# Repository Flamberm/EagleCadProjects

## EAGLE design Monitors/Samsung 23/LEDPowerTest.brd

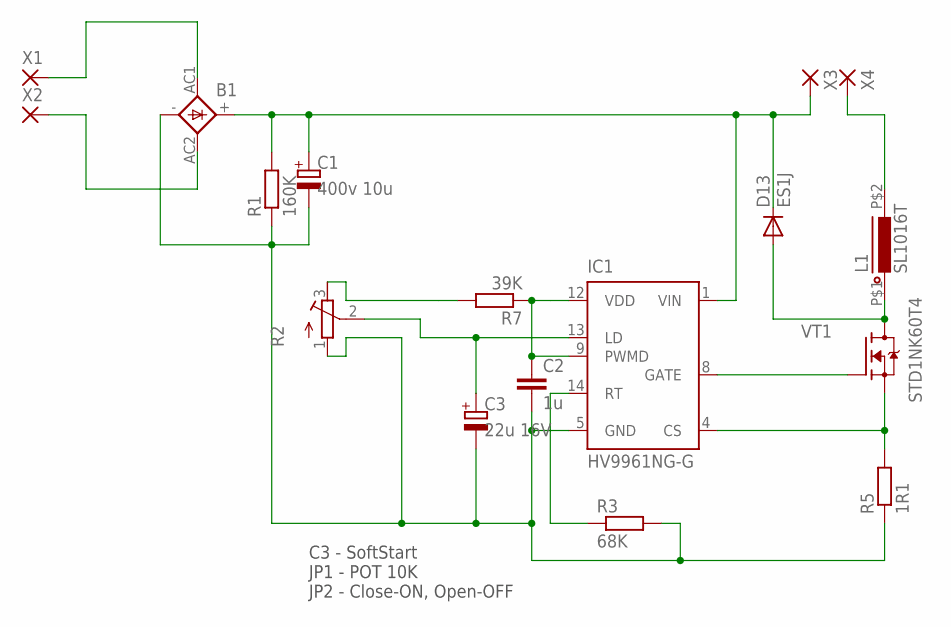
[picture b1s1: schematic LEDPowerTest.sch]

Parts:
B1: BRIDGEDBS; DBS
C1: 400v 10u; E3,5-8
C2: 1u; CAP0805
C3: 22u 16V; CT3528
D13: ES1J; DO214AC
IC1: HV9961NG-G; SOIC-16NG
L1: SL1016T; SL1016
R1: 160K; MF-0125
R2: R_POT3296X; POT-3296X
R3: 68K; RESC2012X50
R5: 1R1; MF-05
R7: 39K; RESC2012X50
VT1: STD1NK60T4; DPAK
X1, X2, X3, X4: WIREPAD-SMD2; PAD-1.27X2.54

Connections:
unnamed: R2.3 (E), R7.2
unnamed: C2.1, IC1.9 (PWMD), IC1.12 (VDD), R7.1
unnamed: B1.AC1, X1.P$1
unnamed: B1.AC2, X2.P$1
unnamed: B1.-, C1.-, C2.2, C3.-, IC1.5 (GND), R1.1, R2.1 (A), R3.2, R5.1
unnamed: C3.+, IC1.13 (LD), R2.2 (S)
unnamed: B1.+, C1.+, D13.C, IC1.1 (VIN), R1.2, X3.P$1
unnamed: IC1.4 (CS), R5.2, VT1.S
unnamed: IC1.14 (RT), R3.1
unnamed: IC1.8 (GATE), VT1.G
unnamed: L1.P$2 (2), X4.P$1
unnamed: D13.A, L1.P$1 (1), VT1.D

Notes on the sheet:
C3 - SoftStart JP1 - POT 10K JP2 - Close-ON, Open-OFF

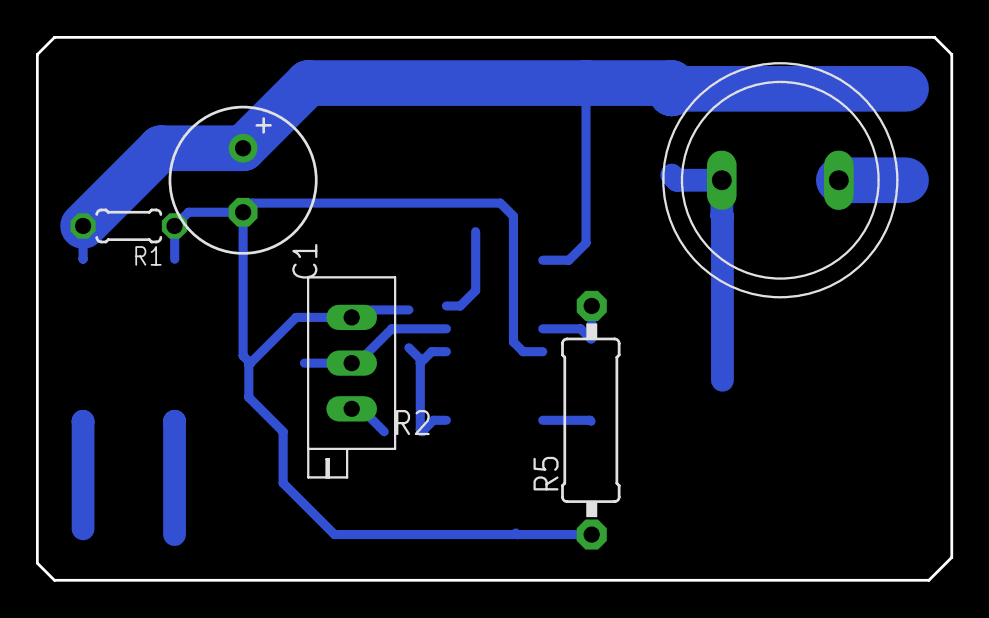
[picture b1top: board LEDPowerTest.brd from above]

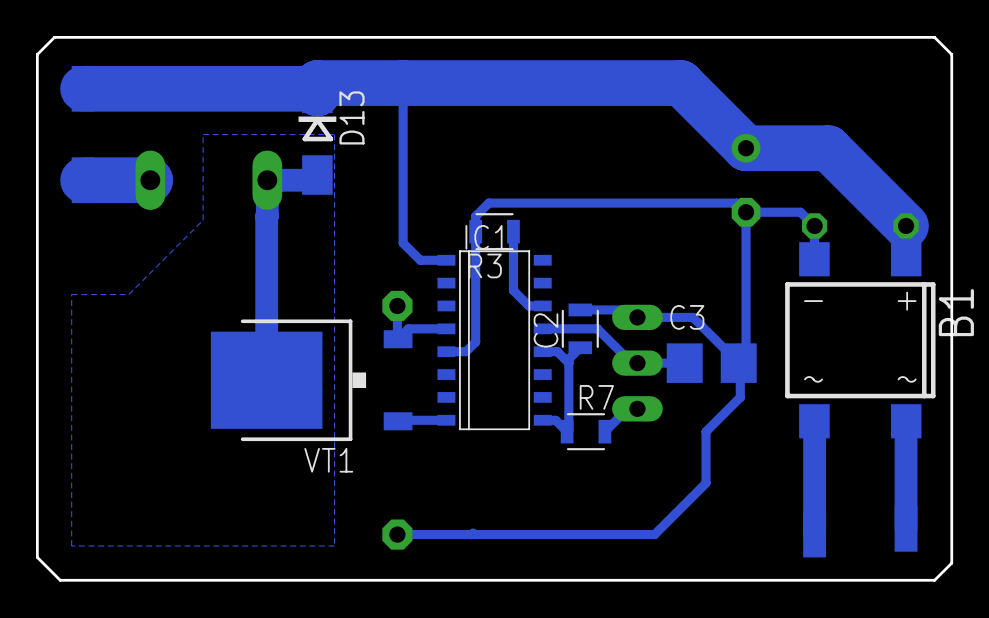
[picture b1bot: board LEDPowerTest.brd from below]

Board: 2 copper layers, 50.8 x 30.2 mm, 17 parts (12 on the bottom side), 12 nets.

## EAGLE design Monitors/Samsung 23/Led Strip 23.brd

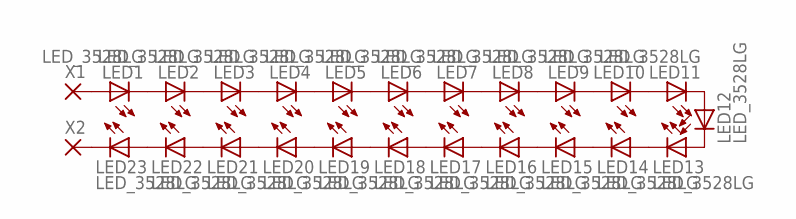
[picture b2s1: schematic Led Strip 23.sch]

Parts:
LED1, LED2, LED3, LED4, LED5, LED6, LED7, LED8, LED9, LED10, LED11, LED12, LED13, LED14, LED15, LED16, LED17, LED18, LED19, LED20, LED21, LED22, LED23: LED_3528LG; LED2835_LG
X1, X2: WIREPAD-SMD2; PAD-1.27X2.54

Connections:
unnamed: LED1.A, X1.P$1
unnamed: LED1.C, LED2.A
unnamed: LED2.C, LED3.A
unnamed: LED3.C, LED4.A
unnamed: LED4.C, LED5.A
unnamed: LED5.C, LED6.A
unnamed: LED6.C, LED7.A
unnamed: LED7.C, LED8.A
unnamed: LED8.C, LED9.A
unnamed: LED9.C, LED10.A
unnamed: LED10.C, LED11.A
unnamed: LED11.C, LED12.A
unnamed: LED12.C, LED13.A
unnamed: LED14.C, LED15.A
unnamed: LED15.C, LED16.A
unnamed: LED16.C, LED17.A
unnamed: LED17.C, LED18.A
unnamed: LED18.C, LED19.A
unnamed: LED19.C, LED20.A
unnamed: LED20.C, LED21.A
unnamed: LED21.C, LED22.A
unnamed: LED22.C, LED23.A
unnamed: LED23.C, X2.P$1
unnamed: LED13.C, LED14.A

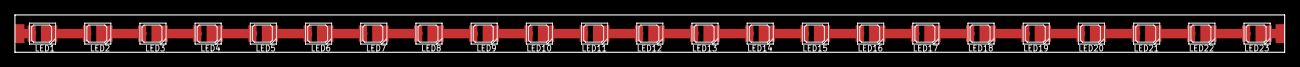
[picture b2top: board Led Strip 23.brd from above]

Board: 2 copper layers, 170.0 x 5.0 mm, 25 parts (0 on the bottom side), 24 nets.

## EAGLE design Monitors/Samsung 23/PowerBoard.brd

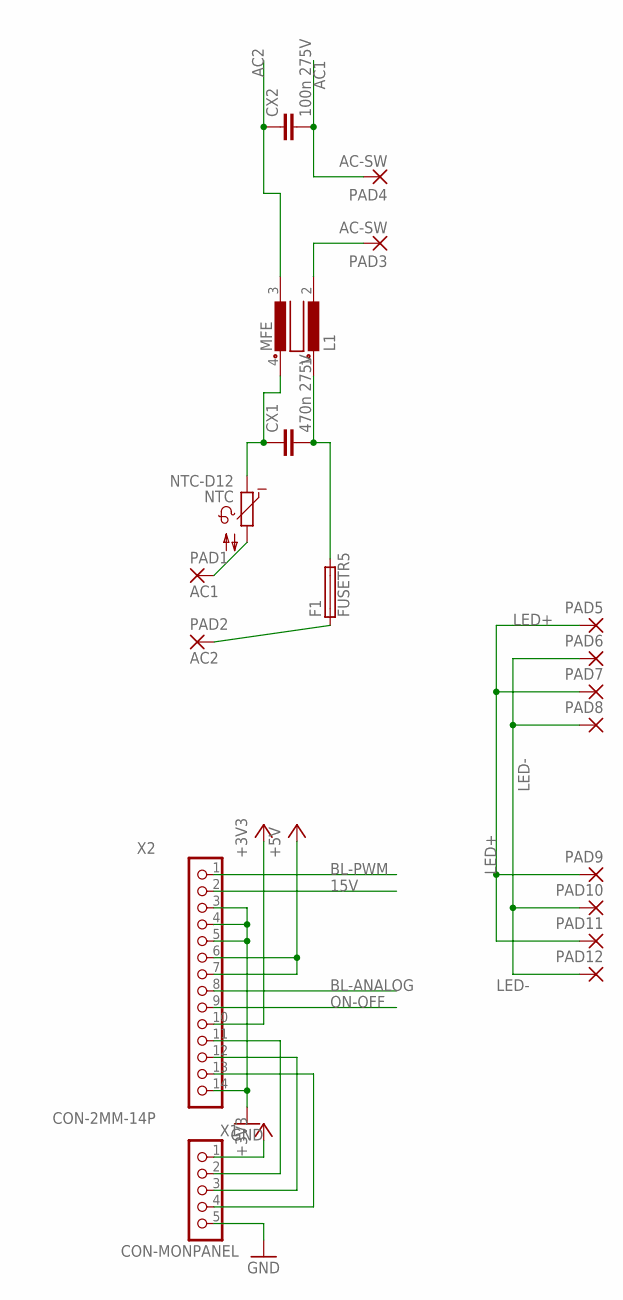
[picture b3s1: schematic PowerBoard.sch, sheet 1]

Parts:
CX1: 470n 275V; XC15B10
CX2: 100n 275V; XC15B6
F1: FUSETR5; TR5
L1: MFE
NTC: NTC-D12
PAD1: AC1; 3,81/1,4
PAD2: AC2; 3,81/1,4
PAD3, PAD4: AC-SW; 2,54/1,1
PAD5, PAD6, PAD7, PAD8, PAD9, PAD10, PAD11, PAD12: 2,54/1,1
X1: CON-MONPANEL; CON-5-PANEL
X2: CON-2MM-14P; CON-14-2MM

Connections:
15V: X2.2
+3V3: X1.1, X2.10
+5V: X2.6, X2.7; also elsewhere on the board
AC1: CX2.2, PAD4.1; also elsewhere on the board
AC2: CX2.1, L1.3 (4); also elsewhere on the board
BL-ANALOG: X2.8
BL-PWM: X2.1; also elsewhere on the board
GND: X1.5, X2.3, X2.4, X2.5, X2.14; also elsewhere on the board
LED+: PAD5.1, PAD7.1, PAD9.1, PAD11.1; also elsewhere on the board
LED-: PAD6.1, PAD8.1, PAD10.1, PAD12.1; also elsewhere on the board
unnamed: X1.2, X2.11
unnamed: X1.3, X2.12
unnamed: X1.4, X2.13
unnamed: NTC.2, PAD1.1
unnamed: F1.1, PAD2.1
unnamed: CX1.1, L1.4 (3), NTC.1
unnamed: CX1.2, F1.2, L1.1
unnamed: L1.2, PAD3.1
ON-OFF: X2.9; also elsewhere on the board

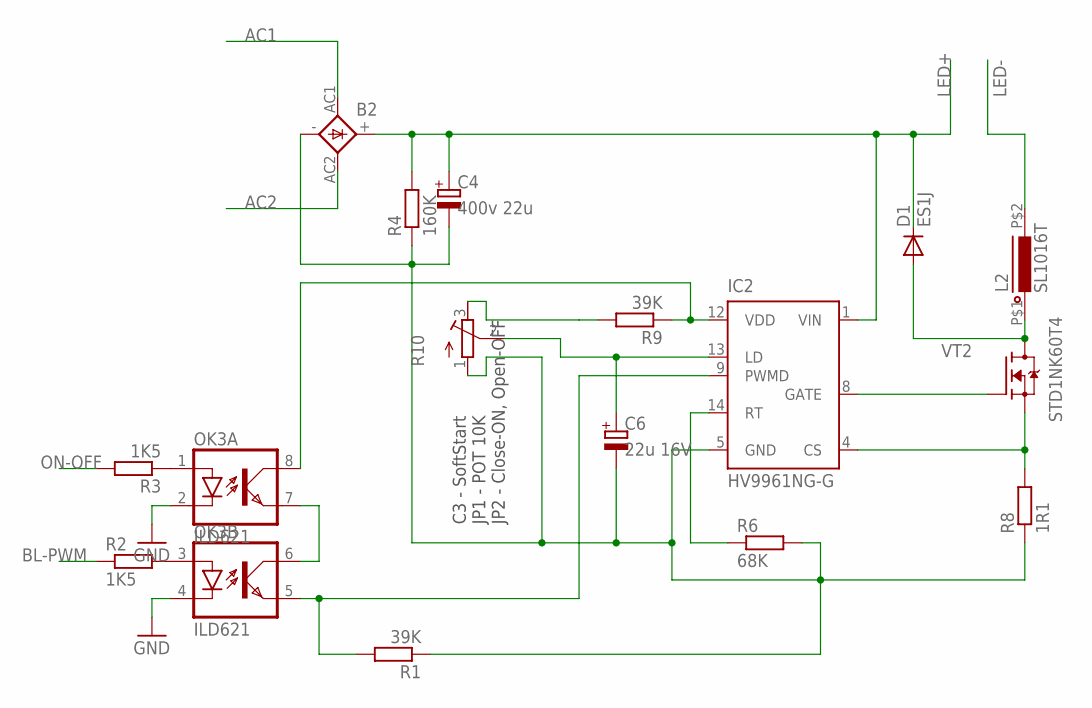
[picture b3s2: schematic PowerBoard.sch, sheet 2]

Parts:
B2: BRIDGEDBS; DBS
C4: 400v 22u; E3,5-8
C6: 22u 16V; CT3528
D1: ES1J; DO214AC
IC2: HV9961NG-G; SOIC-16NG
L2: SL1016T; SL1016
OK3: ILD621; DIL08
R1, R9: 39K; RESC2012X50
R2, R3: 1K5; MF-025
R4: 160K; MF-0125
R6: 68K; RESC2012X50
R8: 1R1; MF-05
R10: R_POT3296X; POT-3296X
VT2: STD1NK60T4; DPAK

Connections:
AC1: B2.AC1; also elsewhere on the board
AC2: B2.AC2; also elsewhere on the board
BL-PWM: R2.1; also elsewhere on the board
GND: OK3.2 (C), OK3.4 (C); also elsewhere on the board
LED+: B2.+, C4.+, D1.C, IC2.1 (VIN), R4.2; also elsewhere on the board
LED-: L2.P$2 (2); also elsewhere on the board
unnamed: OK3.6 (COL), OK3.7 (EMIT)
unnamed: IC2.9 (PWMD), OK3.5 (EMIT), R1.2
unnamed: OK3.1 (A), R3.1
unnamed: OK3.3 (A), R2.2
unnamed: IC2.14 (RT), R6.1
unnamed: IC2.8 (GATE), VT2.G
unnamed: D1.A, L2.P$1 (1), VT2.D
unnamed: IC2.4 (CS), R8.2, VT2.S
unnamed: B2.-, C4.-, C6.-, IC2.5 (GND), R1.1, R4.1, R6.2, R8.1, R10.1 (A)
unnamed: C6.+, IC2.13 (LD), R10.2 (S)
unnamed: R9.2, R10.3 (E)
unnamed: IC2.12 (VDD), OK3.8 (COL), R9.1
ON-OFF: R3.2; also elsewhere on the board

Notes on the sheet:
C3 - SoftStart JP1 - POT 10K JP2 - Close-ON, Open-OFF

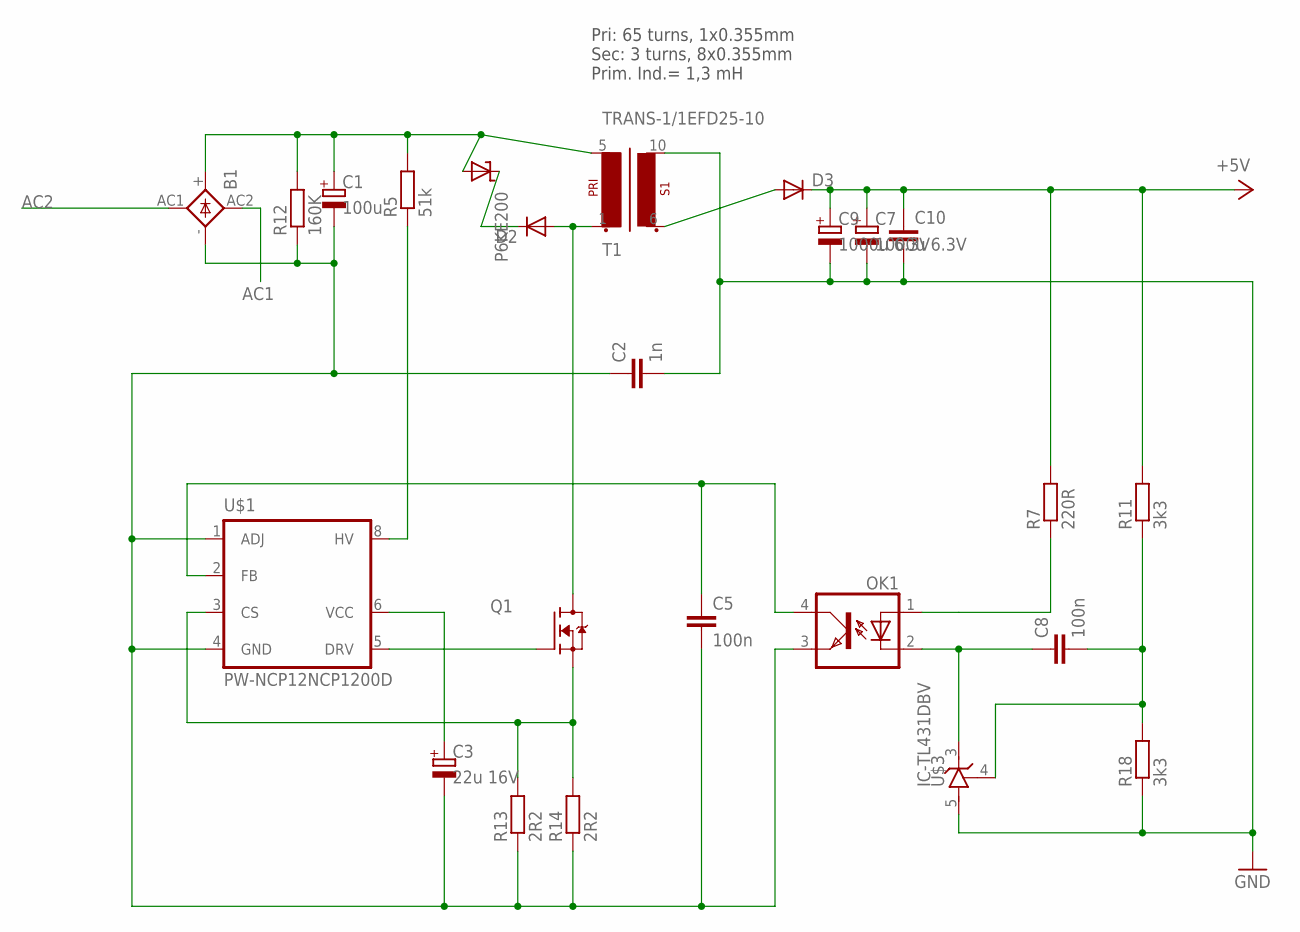
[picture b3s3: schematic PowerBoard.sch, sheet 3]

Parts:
B1: KBL
C1: 100u; E5-13-35-HORIZ
C2: 1n; C050-024X044
C3: 22u 16V; E2,5-7
C5, C8: 100n; CAP1206
C7, C9: 1000u 6.3V; E3,5-8
C10: CAP_0805; CAP0805
D2: DIODE_ES1J; DO214AC
D3: DIODE_TO-220-2; TO220ACS
OK1: OPTOTRANSPC817; DIL04
P6KE200: SUPRESSORDO-204AC; DO15-12
Q1: FET-NTO-220; TO-220V
R5: 51k; SQP-5
R7: 220R; RESC3216X60
R11, R18: 3k3; RESC3216X60
R12: 160K; MF-0125
R13, R14: 2R2; MF-025
T1: TRANS-1/1EFD25-10; EFD25_10PIN
U$1: PW-NCP12NCP1200D; SO8
U$3: IC-TL431DBV; SOT95P280X145-5

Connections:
+5V: C7.+, C9.+, C10.1, D3.C, R7.2, R11.2; also elsewhere on the board
AC1: B1.AC2 (AC1); also elsewhere on the board
AC2: B1.AC1 (AC2); also elsewhere on the board
GND: C2.2, C7.-, C9.-, C10.2, R18.1, T1.10 (S1-2), U$3.5 (A); also elsewhere on the board
unnamed: B1.+, C1.+, P6KE200.A, R5.2, R12.2, T1.5 (P1-2)
unnamed: D2.A, Q1.2 (D), T1.1 (P1-1)
unnamed: R5.1, U$1.8 (HV)
unnamed: C3.+, U$1.6 (VCC)
unnamed: C5.1, OK1.4 (COL), U$1.2 (FB)
unnamed: D2.C, P6KE200.C
unnamed: OK1.1 (A), R7.1
unnamed: Q1.1 (G), U$1.5 (DRV)
unnamed: C8.2, R11.1, R18.2, U$3.4 (R)
unnamed: B1.-, C1.-, C2.1, C3.-, C5.2, OK1.3 (EMIT), R12.1, R13.1, R14.1, U$1.1 (ADJ), U$1.4 (GND)
unnamed: C8.1, OK1.2 (C), U$3.3 (C)
unnamed: Q1.3 (S), R13.2, R14.2, U$1.3 (CS)
unnamed: D3.A, T1.6 (S1-1)

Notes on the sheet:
Pri: 65 turns, 1x0.355mm Sec: 3 turns, 8x0.355mm Prim. Ind.= 1,3 mH

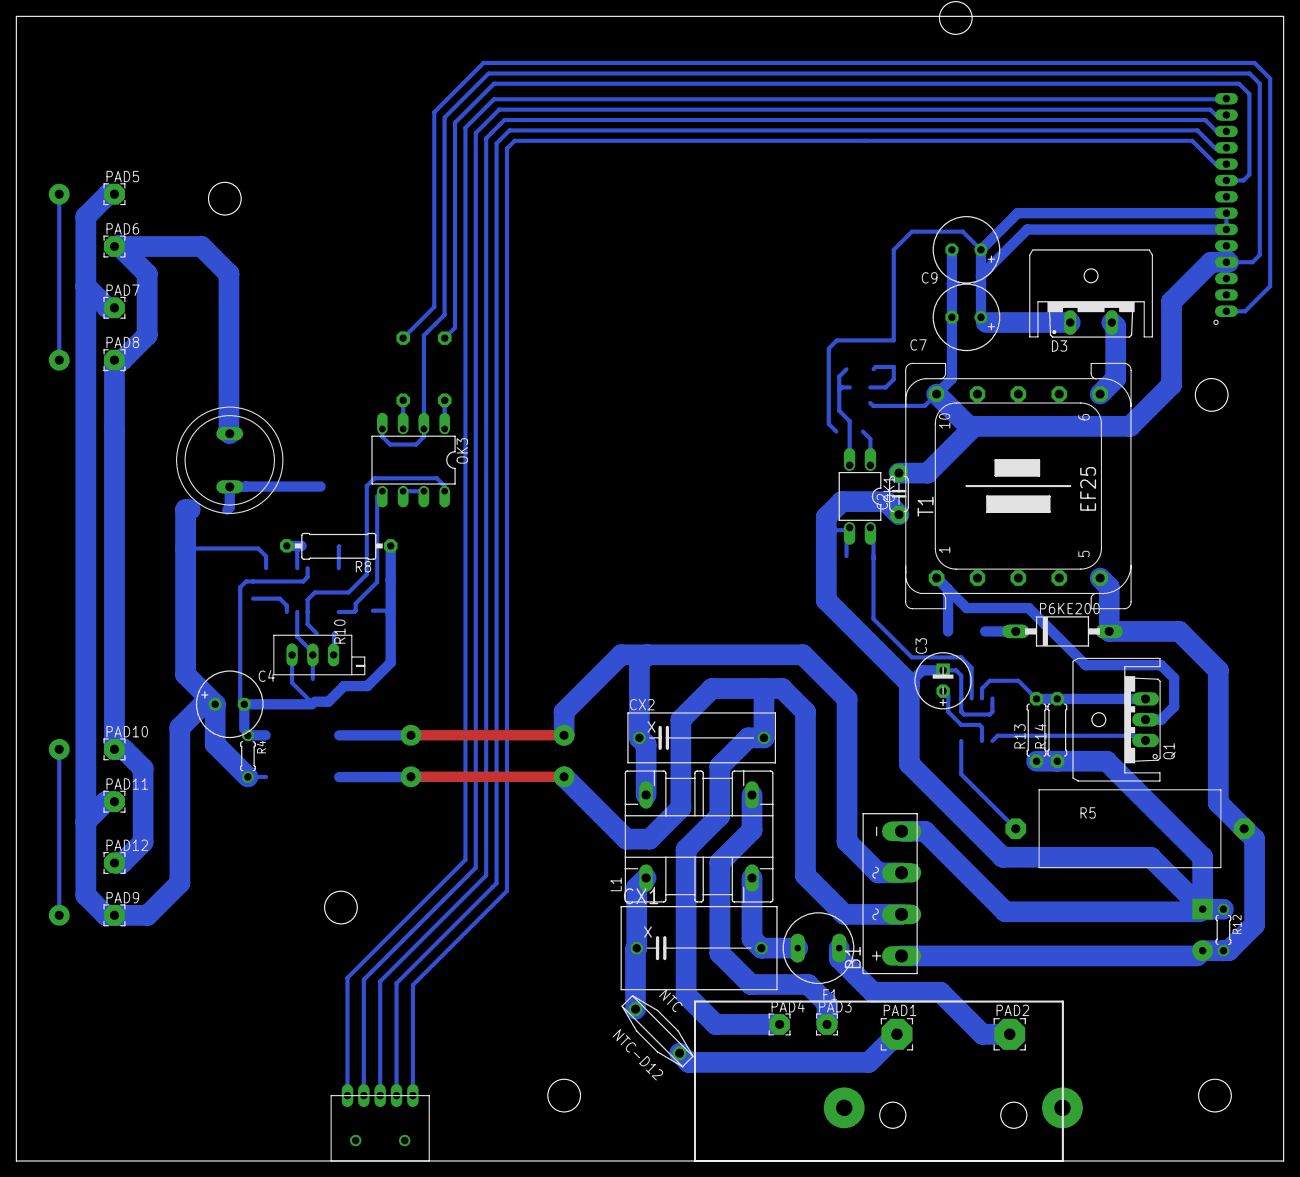
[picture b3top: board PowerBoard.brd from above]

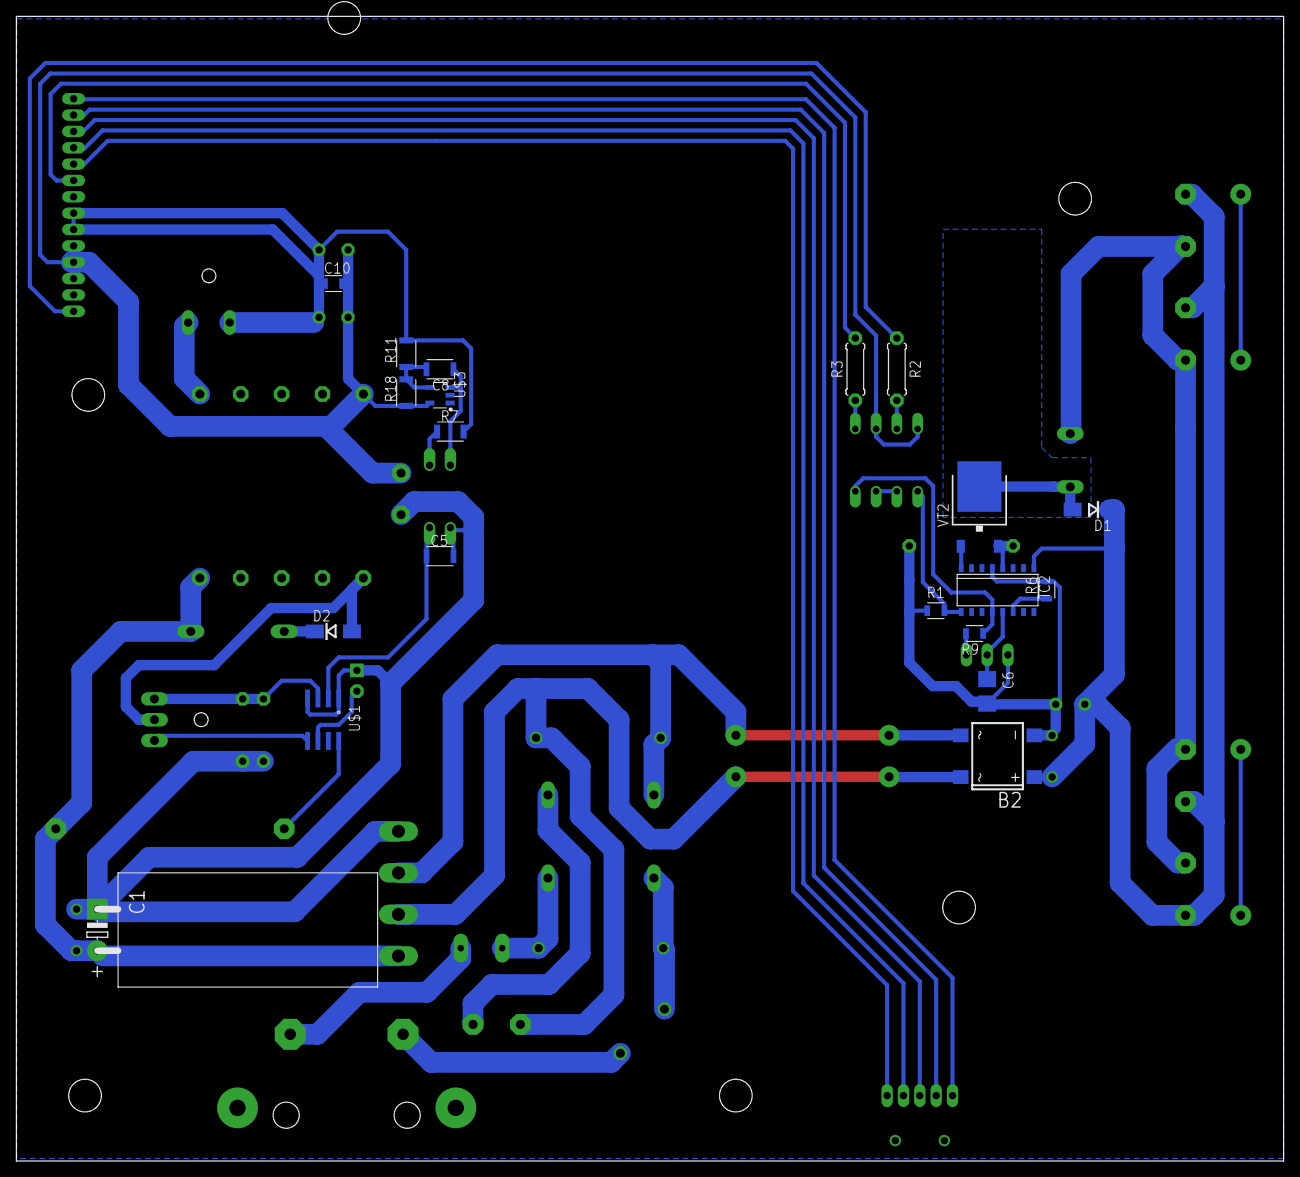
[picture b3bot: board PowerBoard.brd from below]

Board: 2 copper layers, 155.0 x 140.0 mm, 61 parts (20 on the bottom side), 42 nets.

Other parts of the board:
U$2, U$4: SK95-3M3_HOLE

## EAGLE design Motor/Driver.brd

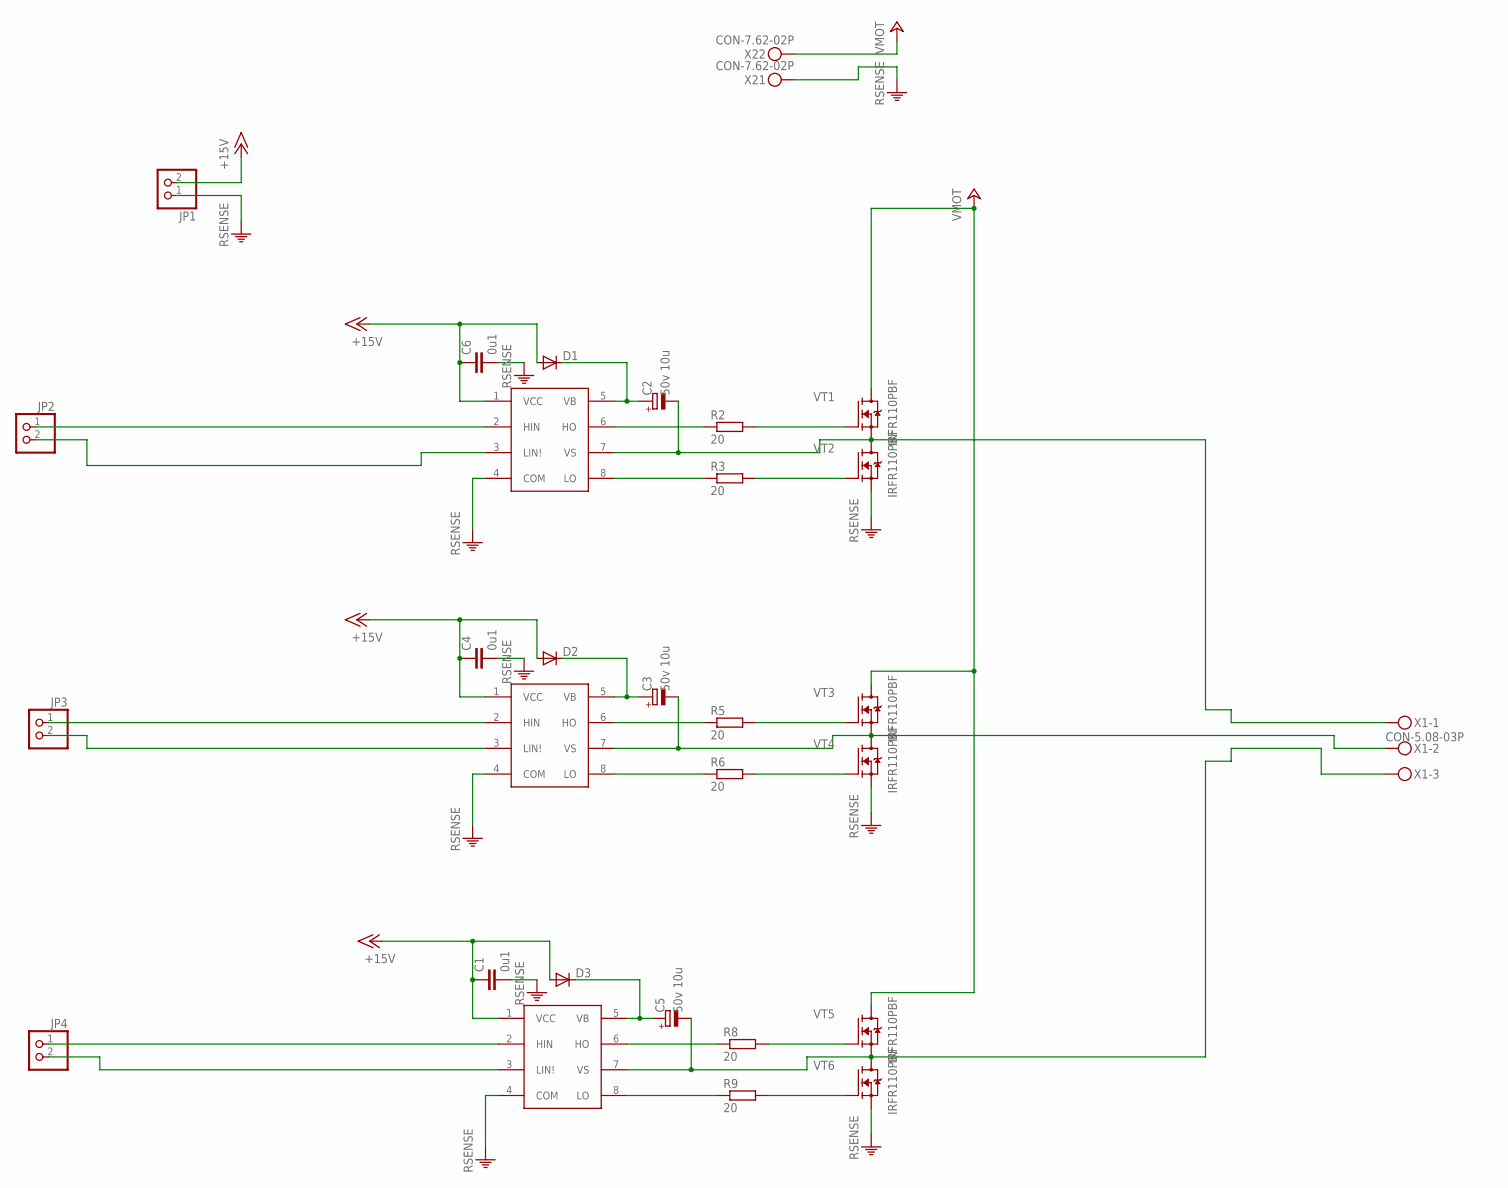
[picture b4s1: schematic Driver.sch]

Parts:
C1, C4, C6: 0u1; C0805
C2, C3, C5: 50v 10u; E2,5-7
D1, D2, D3: DIODE_ES1J; DO214AC
IC-1, IC-2, IC-3: IC-IR2103; SO8
JP1, JP2, JP3, JP4: PINHD-1X2; 1X02
R2, R3, R5, R6, R8, R9: 20; R0805
VT1, VT2, VT3, VT4, VT5, VT6: IRFR110PBF; DPAK
X1: CON-5.08-03P; MKDSN1,5/3-5,08
X2: CON-7.62-02P; KF25C-7.62-02P-13

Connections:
+15V: C1.1, C4.1, C6.1, D1.A, D2.A, D3.A, IC-1.1 (VCC), IC-2.1 (VCC), IC-3.1 (VCC), JP1.2
+24V: VT1.D, VT3.D, VT5.D, X2.P$2
unnamed: C2.-, IC-1.7 (VS), VT1.S, VT2.D, X1.1
unnamed: C2.+, D1.C, IC-1.5 (VB)
unnamed: IC-1.2 (HIN), JP2.1
unnamed: IC-1.3 (LIN!), JP2.2
unnamed: IC-1.8 (LO), R3.1
unnamed: IC-1.6 (HO), R2.1
unnamed: C3.-, IC-2.7 (VS), VT3.S, VT4.D, X1.2
unnamed: C3.+, D2.C, IC-2.5 (VB)
unnamed: IC-2.2 (HIN), JP3.1
unnamed: IC-2.3 (LIN!), JP3.2
unnamed: IC-2.8 (LO), R6.1
unnamed: IC-2.6 (HO), R5.1
unnamed: C5.-, IC-3.7 (VS), VT5.S, VT6.D, X1.3
unnamed: C5.+, D3.C, IC-3.5 (VB)
unnamed: IC-3.2 (HIN), JP4.1
unnamed: IC-3.3 (LIN!), JP4.2
unnamed: IC-3.8 (LO), R9.1
unnamed: IC-3.6 (HO), R8.1
unnamed: R9.2, VT6.G
unnamed: R8.2, VT5.G
unnamed: R5.2, VT3.G
unnamed: R6.2, VT4.G
unnamed: R3.2, VT2.G
unnamed: R2.2, VT1.G
RSENSE: C1.2, C4.2, C6.2, IC-1.4 (COM), IC-2.4 (COM), IC-3.4 (COM), JP1.1, VT2.S, VT4.S, VT6.S, X2.P$1

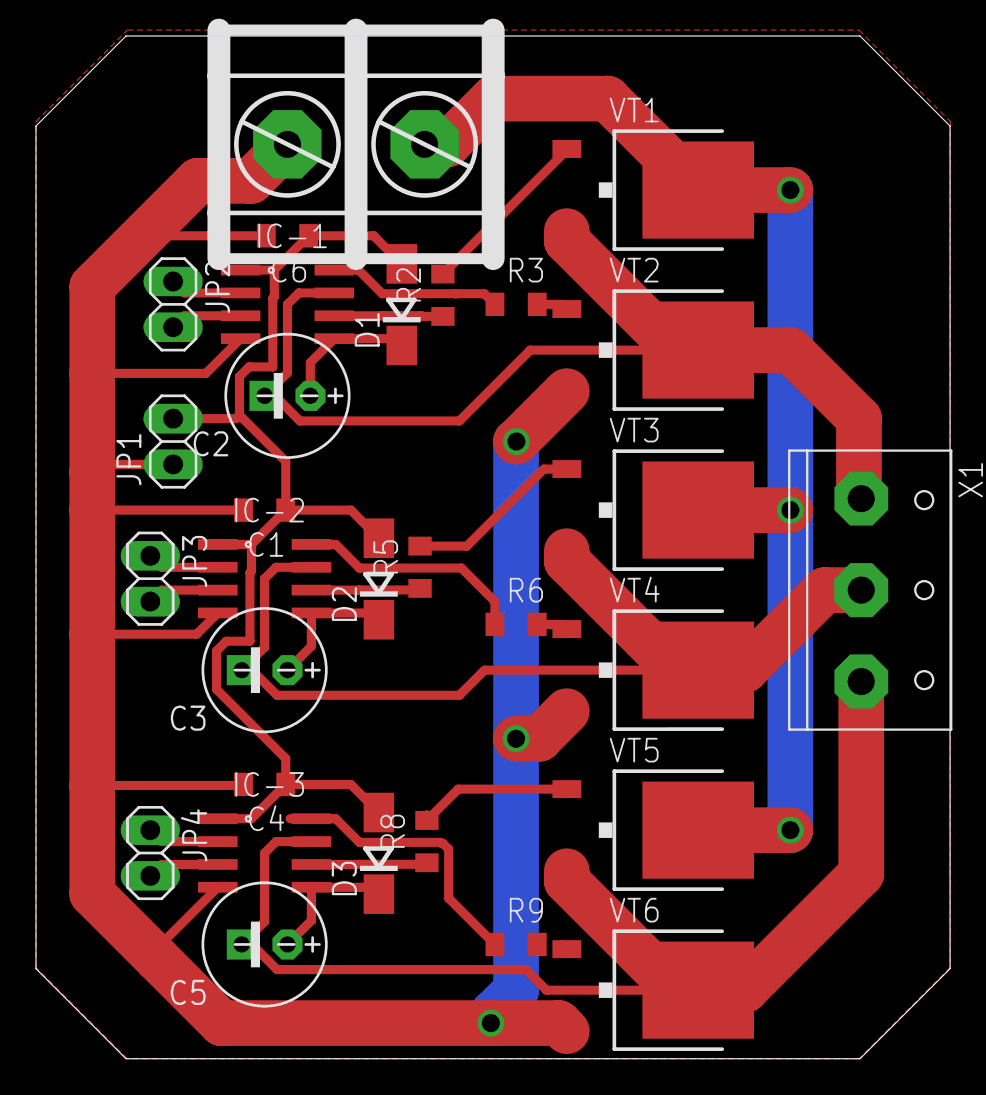
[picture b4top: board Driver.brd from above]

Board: 2 copper layers, 50.8 x 56.8 mm, 30 parts (0 on the bottom side), 27 nets.

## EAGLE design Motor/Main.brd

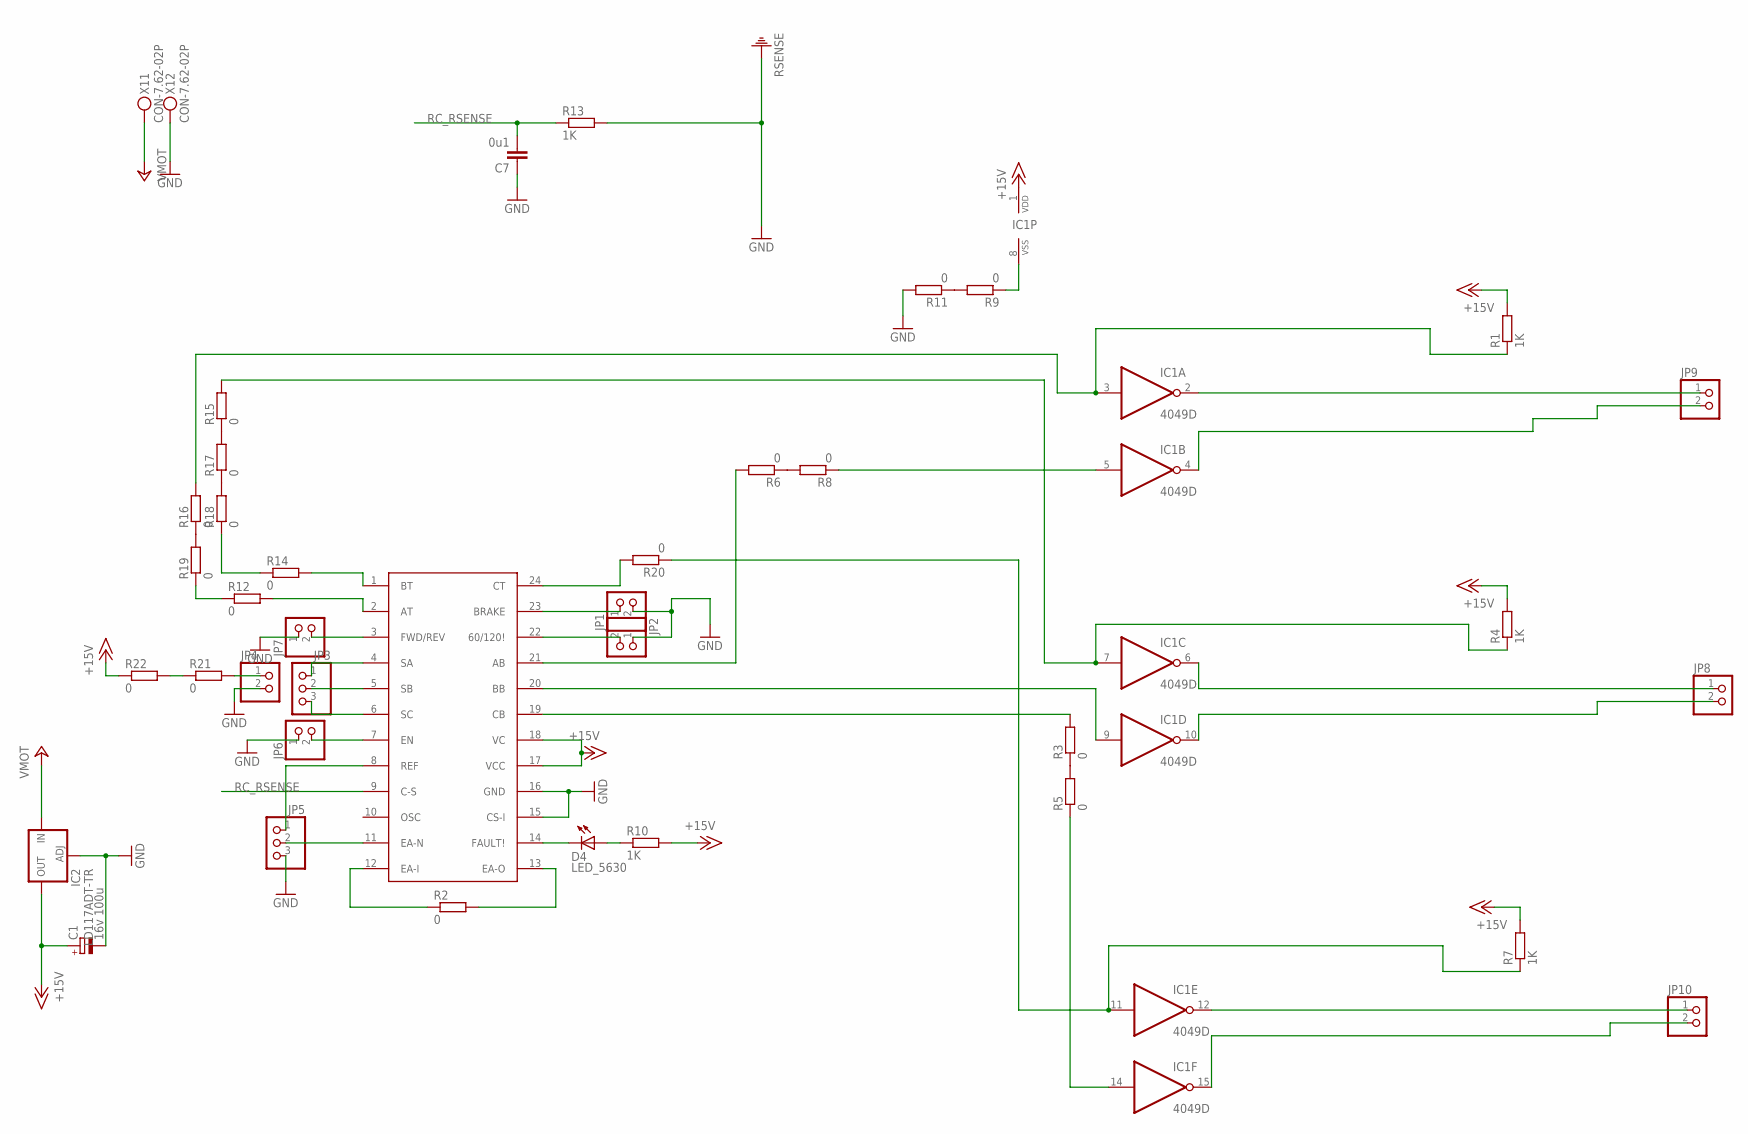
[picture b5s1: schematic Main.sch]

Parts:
C1: 16v 100u; E2,5-7
C7: 0u1; C0805
D4: LED_5630; LED5730
IC1: 4049D; SO16
IC2: LD117ADT-TR; DPACK
JP1, JP2, JP4, JP6, JP7, JP8, JP9, JP10: PINHD-1X2; 1X02
JP3, JP5: PINHD-1X3; 1X03
R1, R4, R7, R10, R13: 1K; R0805
R2, R3, R5, R6, R8, R11, R12, R14, R15, R16, R17, R18, R19, R20, R21, R22: 0; R0805
R9: 0; R1206
U$1: IC-MC33035-D; SO24W
X1: CON-7.62-02P; KF25C-7.62-02P-13

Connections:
+15V: C1.+, IC1.1 (VDD), IC2.4 (OUT), R1.2, R4.2, R7.2, R10.2, R22.1, U$1.17 (VCC), U$1.18 (VC)
+24V: IC2.3 (IN), X1.P$1
GND: C1.-, C7.1, IC2.1 (ADJ), JP1.2, JP2.1, JP4.2, JP5.3, JP6.1, JP7.1, R11.2, R13.2, U$1.15 (CS-I), U$1.16 (GND), X1.P$2
unnamed: R2.2, U$1.13 (EA-O)
unnamed: IC1.14 (I), R5.1
unnamed: IC1.2 (O), JP9.1
unnamed: IC1.4 (O), JP9.2
unnamed: R3.1, R5.2
unnamed: R6.1, R8.2
unnamed: IC1.5 (I), R8.1
unnamed: R9.2, R11.1
unnamed: IC1.6 (O), JP8.1
unnamed: IC1.10 (O), JP8.2
unnamed: IC1.8 (VSS), R9.1
unnamed: R14.2, U$1.1 (BT)
unnamed: R12.2, U$1.2 (AT)
unnamed: R14.1, R18.1
unnamed: IC1.12 (O), JP10.1
unnamed: IC1.15 (O), JP10.2
unnamed: R12.1, R19.1
unnamed: R15.1, R17.2
unnamed: IC1.3 (I), R1.1, R16.2
unnamed: IC1.7 (I), R4.1, R15.2
unnamed: IC1.11 (I), R7.1, R20.1
unnamed: JP1.1, U$1.23 (BRAKE)
unnamed: JP2.2, U$1.22 (60/120!)
unnamed: R6.2, U$1.21 (AB)
unnamed: IC1.9 (I), U$1.20 (BB)
unnamed: R3.2, U$1.19 (CB)
unnamed: R17.1, R18.2
unnamed: R16.1, R19.2
unnamed: R20.2, U$1.24 (CT)
unnamed: JP4.1, R21.2
unnamed: R21.1, R22.2
unnamed: JP3.1, U$1.4 (SA)
unnamed: JP3.2, U$1.5 (SB)
unnamed: JP3.3, U$1.6 (SC)
unnamed: R2.1, U$1.12 (EA-I)
unnamed: JP5.1, U$1.8 (REF)
unnamed: JP5.2, U$1.11 (EA-N)
unnamed: JP6.2, U$1.7 (EN)
unnamed: JP7.2, U$1.3 (FWD/REV)
unnamed: D4.C, U$1.14 (FAULT!)
unnamed: D4.A, D4.A1 (A), R10.1
RC_RSENSE: C7.2, R13.1, U$1.9 (C-S)

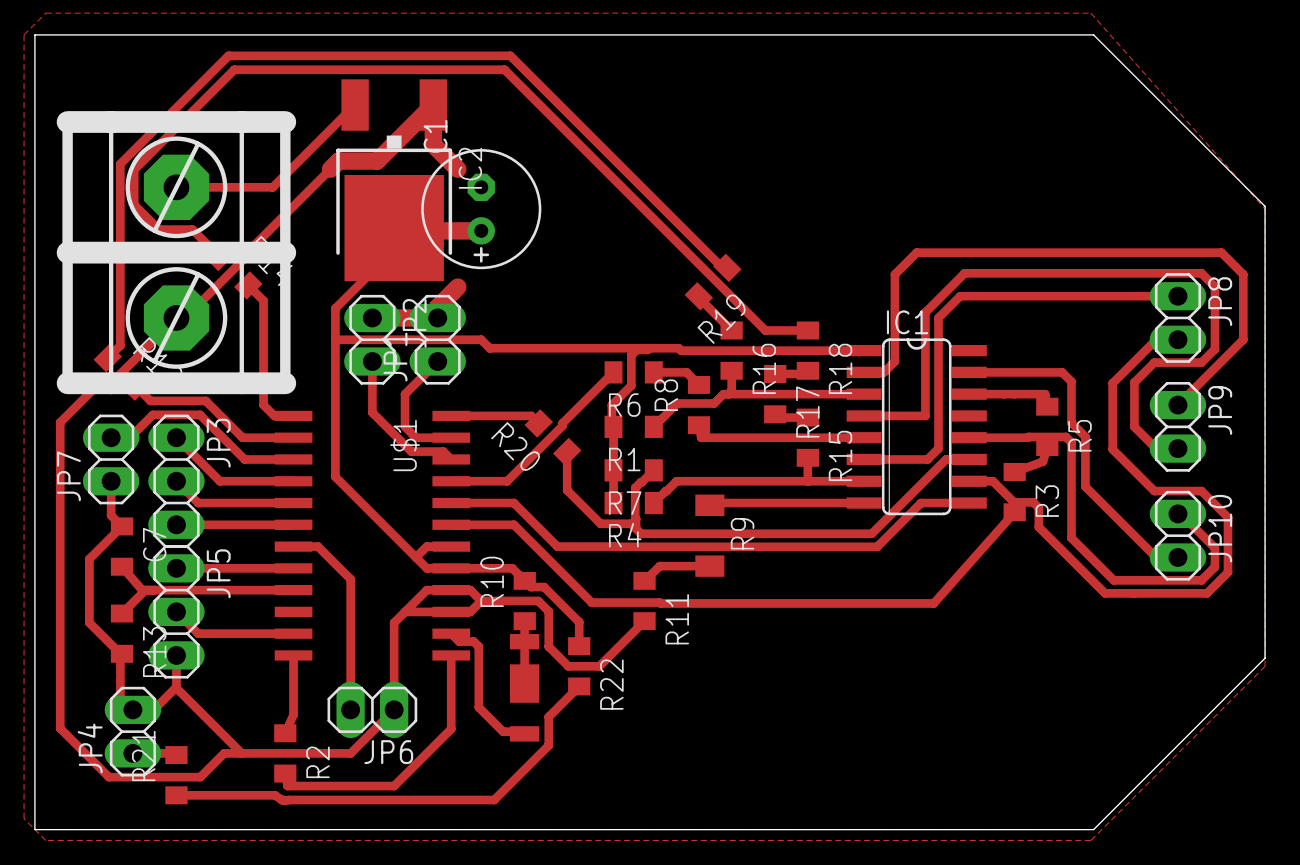
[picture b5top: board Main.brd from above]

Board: 2 copper layers, 71.8 x 46.4 mm, 39 parts (0 on the bottom side), 45 nets.

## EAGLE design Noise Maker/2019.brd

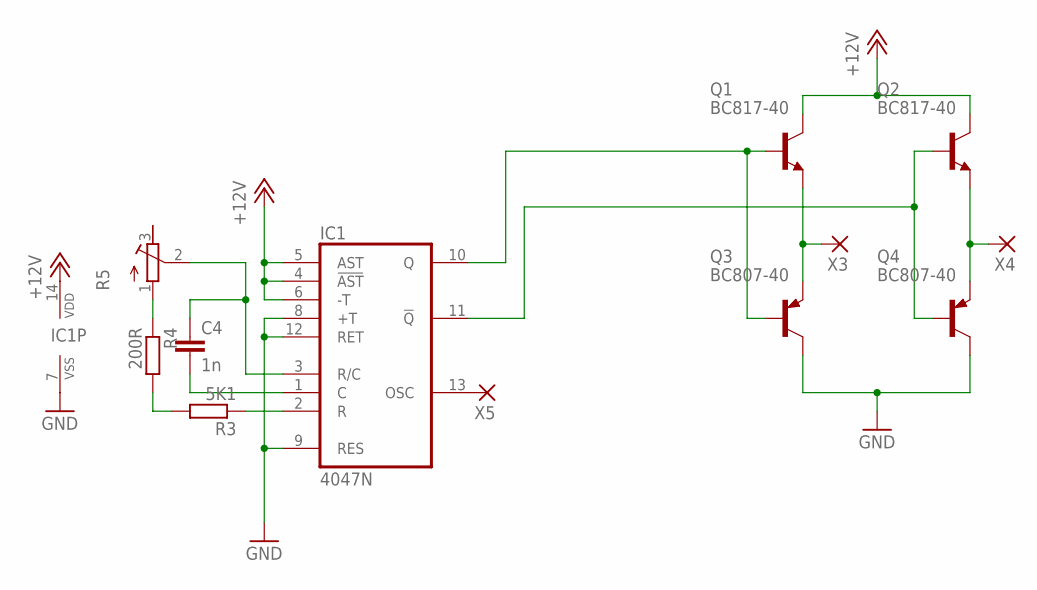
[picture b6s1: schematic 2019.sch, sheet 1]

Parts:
C4: 1n; CAP0805
IC1: 4047N; DIL14
Q1, Q2: BC817-40; SOT95P240X115-3
Q3, Q4: BC807-40; SOT95P240X115-3
R3: 5K1; RESC2012X50
R4: 200R; RESC2012X50
R5: R_POT3296X; POT-3296X
X3, X4, X5: WIREPAD-SMD2; PAD-1.27X2.54

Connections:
+12V: IC1.4 (!AST), IC1.5 (AST), IC1.6 (-T), IC1.14 (VDD), Q1.3 (C), Q2.3 (C); also elsewhere on the board
GND: IC1.7 (VSS), IC1.8 (+T), IC1.9 (RES), IC1.12 (RET), Q3.3 (C), Q4.3 (C); also elsewhere on the board
unnamed: C4.1, IC1.3 (R/C), R5.2 (S)
unnamed: C4.2, IC1.1 (C)
unnamed: IC1.2 (R), R3.1
unnamed: R3.2, R4.2
unnamed: R4.1, R5.1 (A)
unnamed: IC1.10 (Q), Q1.1 (B), Q3.1 (B)
unnamed: IC1.11 (!Q), Q2.1 (B), Q4.1 (B)
unnamed: Q1.2 (E), Q3.2 (E), X3.P$1
unnamed: Q2.2 (E), Q4.2 (E), X4.P$1
unnamed: IC1.13 (OSC), X5.P$1

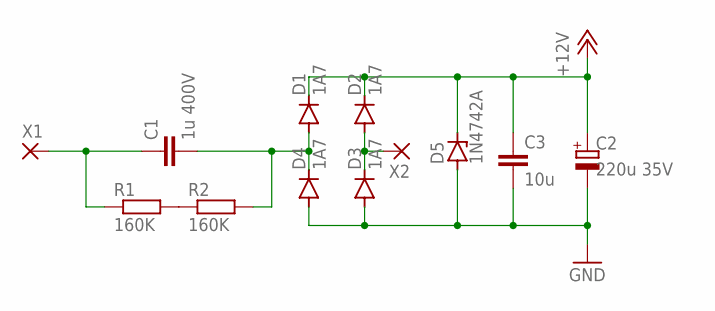
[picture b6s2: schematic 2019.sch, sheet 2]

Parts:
C1: 1u 400V; C225-108X268
C2: 220u 35V; E2,5-7
C3: 10u; CAP1210
D1, D2, D3, D4: 1A7; D-5
D5: 1N4742A; DO41Z10
R1, R2: 160K; MF-0125
X1, X2: WIREPAD-SMD2; PAD-1.27X2.54

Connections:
+12V: C2.+, C3.1, D1.C, D2.C, D5.C; also elsewhere on the board
GND: C2.-, C3.2, D3.A, D4.A, D5.A; also elsewhere on the board
unnamed: C1.1, R1.1, X1.P$1
unnamed: R1.2, R2.1
unnamed: C1.2, D1.A, D4.C, R2.2
unnamed: D2.A, D3.C, X2.P$1

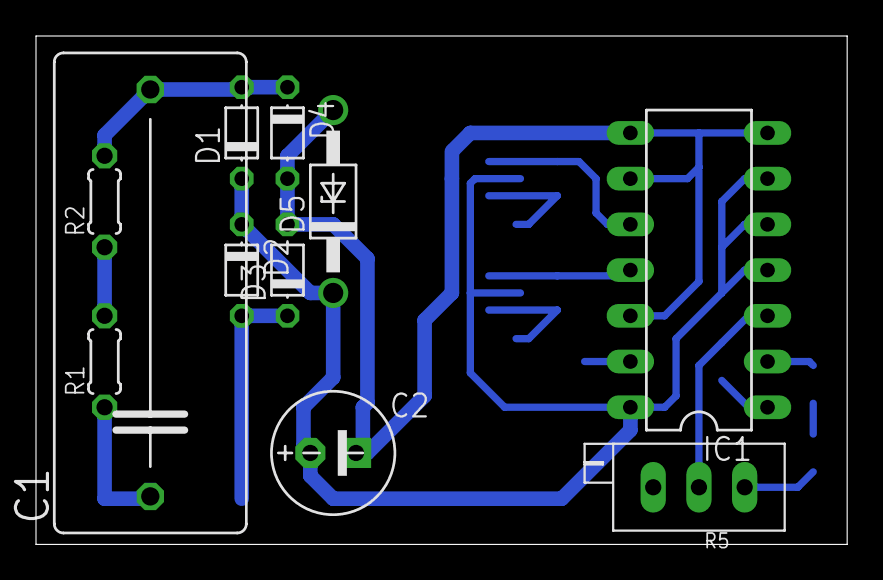
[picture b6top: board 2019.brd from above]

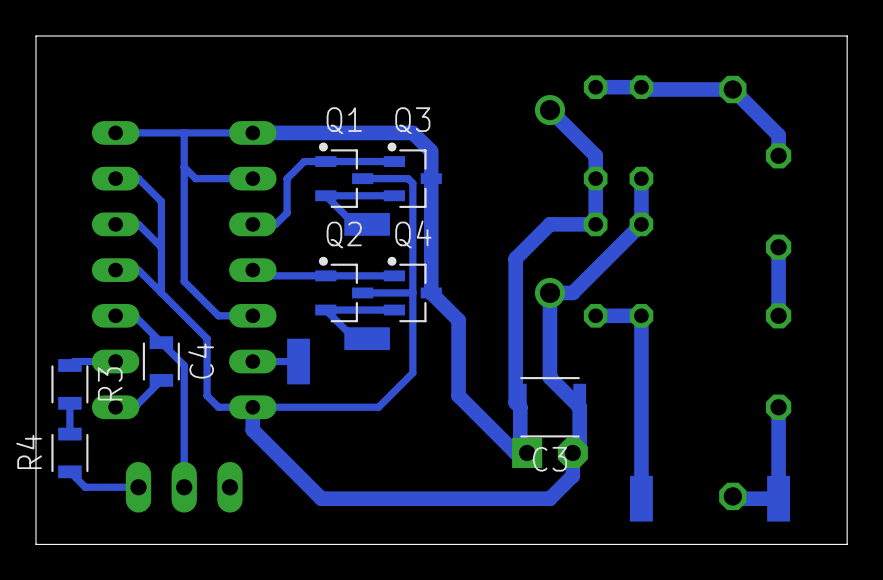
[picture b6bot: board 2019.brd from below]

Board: 2 copper layers, 45.1 x 28.2 mm, 24 parts (13 on the bottom side), 16 nets.
